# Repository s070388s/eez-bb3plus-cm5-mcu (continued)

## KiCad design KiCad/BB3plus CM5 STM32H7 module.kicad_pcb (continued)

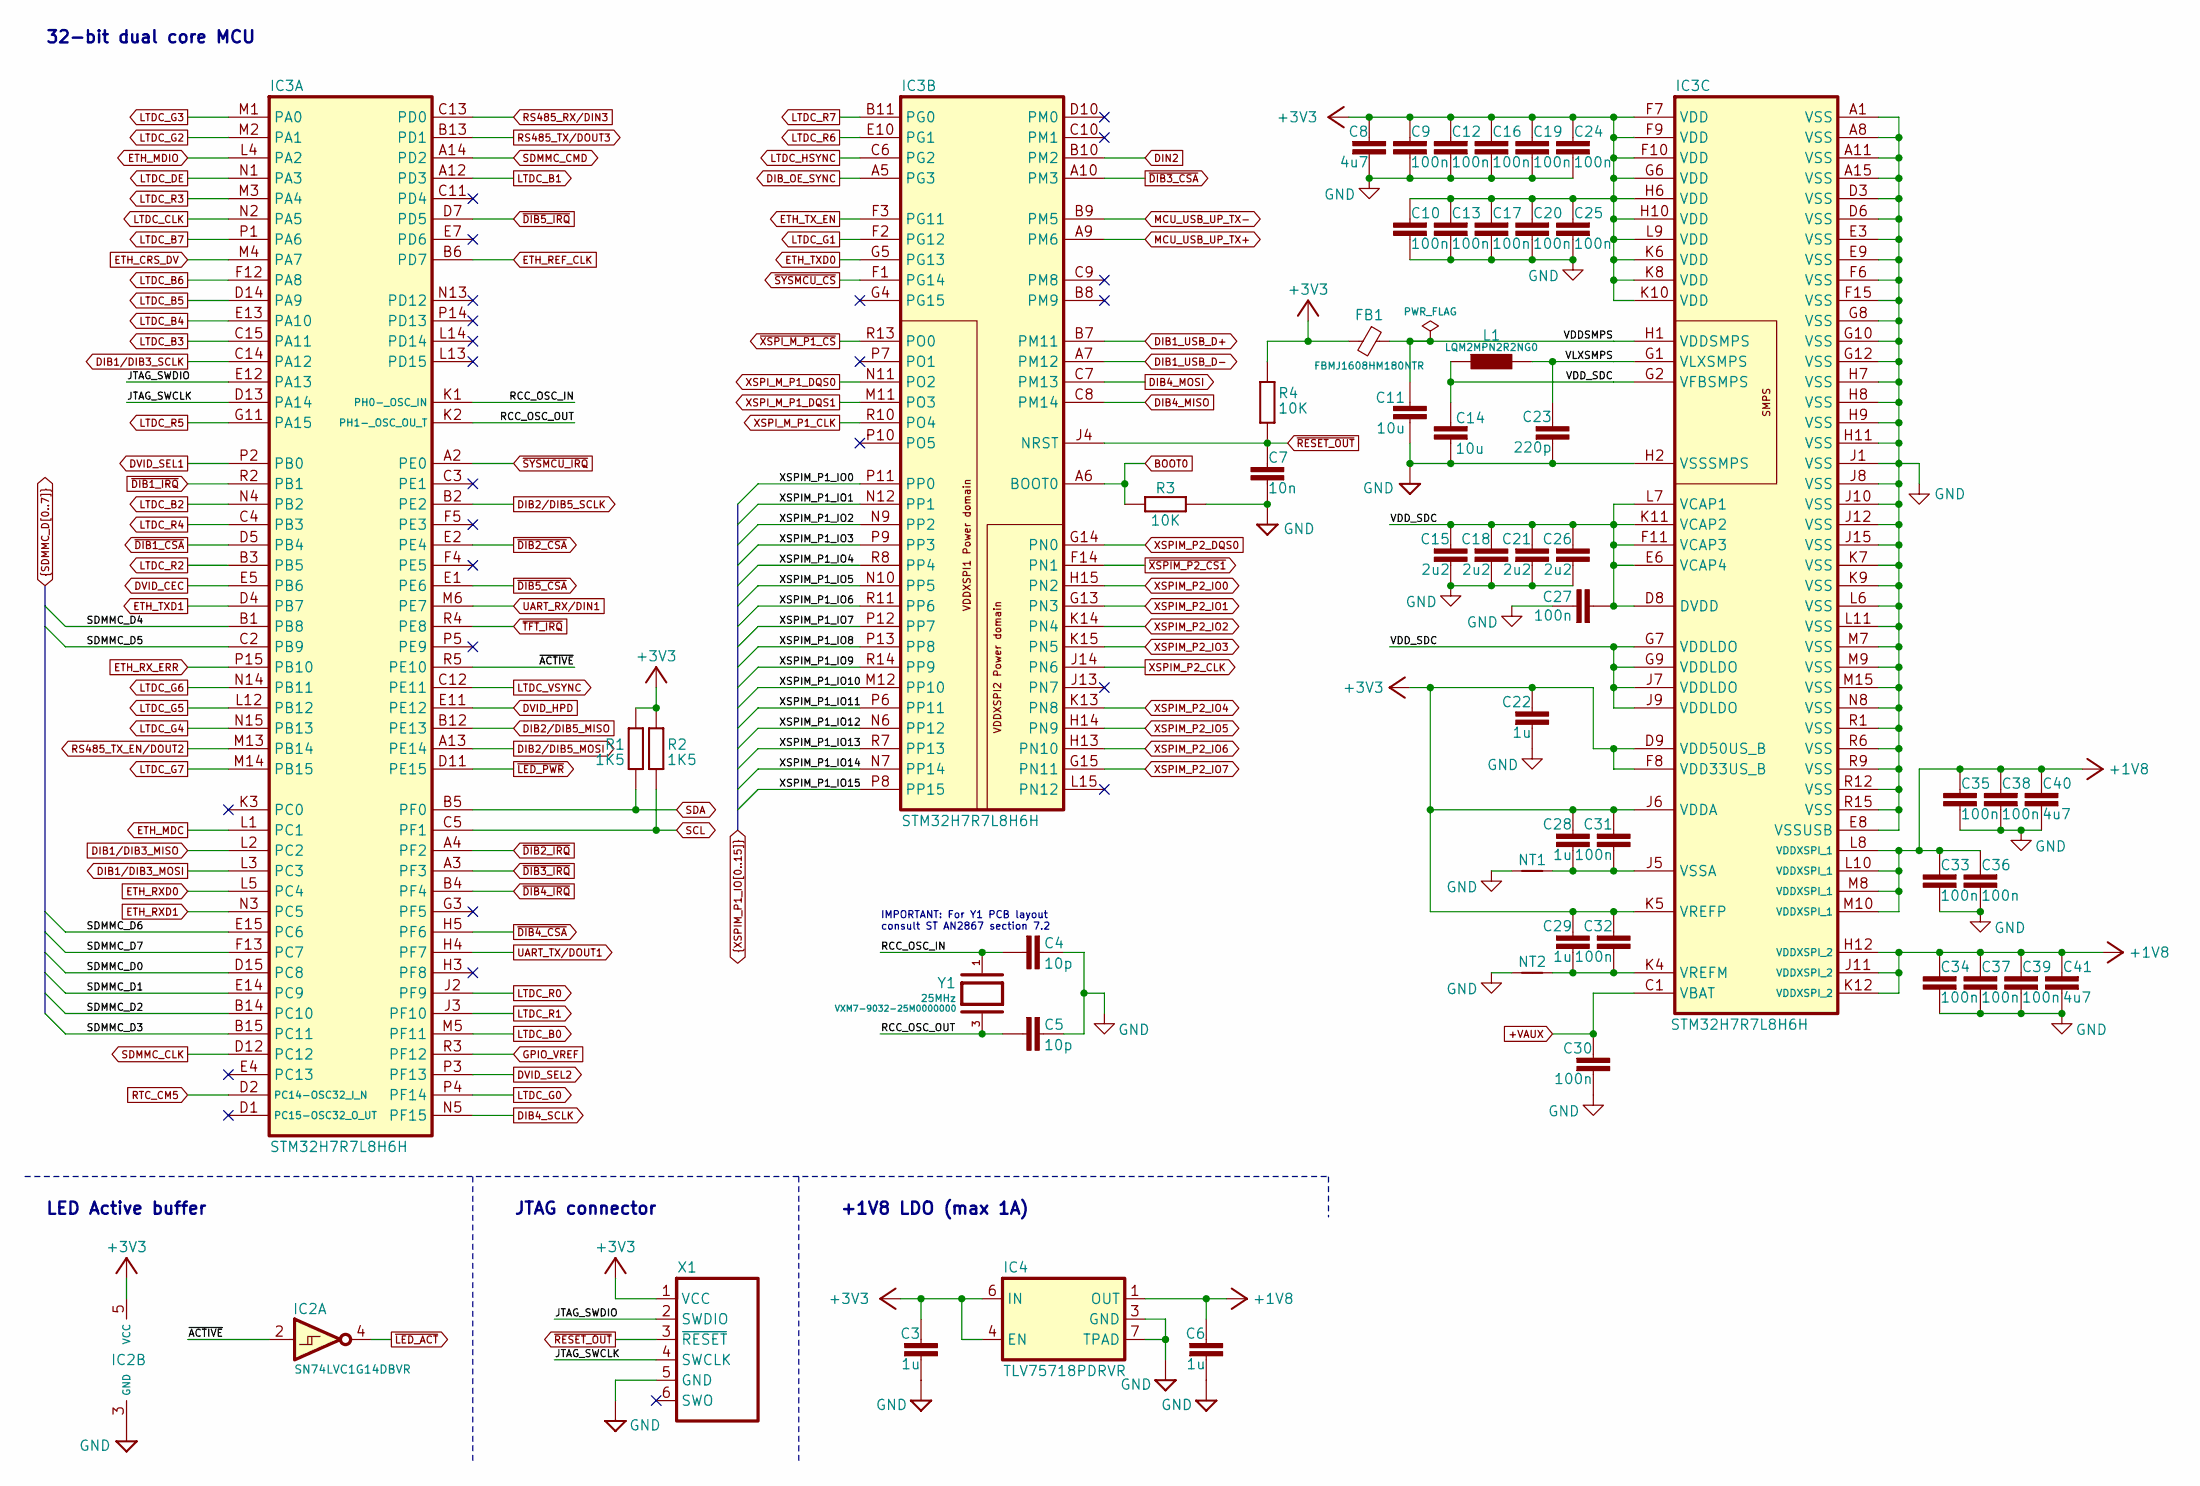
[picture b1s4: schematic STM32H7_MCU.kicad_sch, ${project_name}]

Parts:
C3, C6, C22, C28, C29: 1u; C_0402_1005Metric; DigiKey 490-GRM155C81A105MA12DCT-ND
C4, C5: 10p; C_0402_1005Metric; DigiKey 490-7299-1-ND
C7: 10n; C_0402_1005Metric; DigiKey 490-6309-1-ND
C8, C40, C41: 4u7; C_0603_1608Metric; DigiKey 1276-1044-1-ND
C9, C10, C12, C13, C16, C17, C19, C20, C24, C25, C27, C30, C31, C32, C33, C34, C35, C36, C37, C38, C39: 100n; C_0402_1005Metric; DigiKey 490-6287-1-ND
C11, C14: 10u; C_0603_1608Metric; DigiKey 1276-1052-6-ND
C15, C18, C21, C26: 2u2; C_0402_1005Metric; DigiKey 490-GRM155C71A225KE11JCT-ND
C23: 220p; C_0402_1005Metric; DigiKey 1276-6762-1-ND
FB1: FBMJ1608HM180NTR; BEAD0603; DigiKey 587-3251-2-ND
IC2: SN74LVC1G14DBVR; DBV5; DigiKey 296-11607-1-ND
IC3: STM32H7R7L8H6H; TFBGA225_13X13_STM; DigiKey 497-STM32H7R7L8H6H-ND
IC4: TLV75718PDRVR; DRV0006A; DigiKey 296-50006-1-ND
L1: LQM2MPN2R2NG0; 0806; DigiKey 490-7786-2-ND
NT1, NT2: NetTie_2; NetTie-2_SMD_Pad0.2mm
R1, R2: 1K5; R_0402_1005Metric; DigiKey 311-1.50KLRCT-ND
R3, R4: 10K; R_0402_1005Metric; DigiKey 311-10.0KLRCT-ND
X1: TC2030
Y1: VXM7-9032-25M0000000; XTAL_403C11A24M00000; DigiKey 150-VXM7-9032-25M0000000CT-ND

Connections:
+1V8: C6.1, C33.1, C34.1, C35.1, C36.1, C37.1, C38.1, C39.1, C40.1, C41.1, IC3.H12 (VDDXSPI_2), IC3.J11 (VDDXSPI_2), IC3.K12 (VDDXSPI_2), IC3.L8 (VDDXSPI_1), IC3.L10 (VDDXSPI_1), IC3.M8 (VDDXSPI_1), IC3.M10 (VDDXSPI_1), IC4.1 (OUT); also elsewhere on the board
+3V3: C3.1, C8.1, C9.1, C10.1, C12.1, C13.1, C16.1, C17.1, C19.1, C20.1, C22.1, C24.1, C25.1, C28.1, C29.1, C31.1, C32.1, FB1.2, IC2.5 (VCC), IC3.D9 (VDD50US_B), IC3.F7 (VDD), IC3.F8 (VDD33US_B), IC3.F9 (VDD), IC3.F10 (VDD), IC3.G6 (VDD), IC3.H6 (VDD), IC3.H10 (VDD), IC3.J6 (VDDA), IC3.K5 (VREFP), IC3.K6 (VDD), IC3.K8 (VDD), IC3.K10 (VDD), IC3.L9 (VDD), IC4.4 (EN), IC4.6 (IN), R1.2, R2.2, R4.2, X1.1 (VCC); also elsewhere on the board
+VAUX: C30.1, IC3.C1 (VBAT); also elsewhere on the board
/STM32H7 MCU/JTAG_SWCLK: IC3.D13 (PA14), X1.4 (SWCLK)
/STM32H7 MCU/JTAG_SWDIO: IC3.E12 (PA13), X1.2 (SWDIO)
/STM32H7 MCU/RCC_OSC_IN: C4.2, IC3.K1 (PH0-_OSC_IN), Y1.1
/STM32H7 MCU/RCC_OSC_OUT: C5.2, IC3.K2 (PH1-_OSC_OU_T), Y1.3
/STM32H7 MCU/VDDSMPS: C11.2, FB1.1, IC3.H1 (VDDSMPS)
/STM32H7 MCU/VDD_SDC: C14.2, C15.1, C18.1, C21.1, C26.1, C27.2, IC3.D8 (DVDD), IC3.E6 (VCAP4), IC3.F11 (VCAP3), IC3.G2 (VFBSMPS), IC3.G7 (VDDLDO), IC3.G9 (VDDLDO), IC3.J7 (VDDLDO), IC3.J9 (VDDLDO), IC3.K11 (VCAP2), IC3.L7 (VCAP1), L1.1
/STM32H7 MCU/VLXSMPS: C23.1, IC3.G1 (VLXSMPS), L1.2
/STM32H7 MCU/~ACTIVE: IC2.2 (A), IC3.R5 (PE10)
BOOT0: IC3.A6 (BOOT0), R3.1; also elsewhere on the board
DIB1_USB_D+: IC3.B7 (PM11); also elsewhere on the board
DIB1_USB_D-: IC3.A7 (PM12); also elsewhere on the board
DIB1/DIB3_MISO: IC3.L2 (PC2); also elsewhere on the board
DIB1/DIB3_MOSI: IC3.L3 (PC3); also elsewhere on the board
DIB1/DIB3_SCLK: IC3.C14 (PA12); also elsewhere on the board
DIB2/DIB5_MISO: IC3.B12 (PE13); also elsewhere on the board
DIB2/DIB5_MOSI: IC3.A13 (PE14); also elsewhere on the board
DIB2/DIB5_SCLK: IC3.B2 (PE2); also elsewhere on the board
DIB4_MISO: IC3.C8 (PM14); also elsewhere on the board
DIB4_MOSI: IC3.C7 (PM13); also elsewhere on the board
DIB4_SCLK: IC3.N5 (PF15); also elsewhere on the board
DIB_OE_SYNC: IC3.A5 (PG3); also elsewhere on the board
DIN2: IC3.B10 (PM2); also elsewhere on the board
DVID_CEC: IC3.E5 (PB6); also elsewhere on the board
DVID_HPD: IC3.E11 (PE12); also elsewhere on the board
DVID_SEL1: IC3.P2 (PB0); also elsewhere on the board
DVID_SEL2: IC3.P3 (PF13); also elsewhere on the board
ETH_CRS_DV: IC3.M4 (PA7); also elsewhere on the board
ETH_MDC: IC3.L1 (PC1); also elsewhere on the board
ETH_MDIO: IC3.L4 (PA2); also elsewhere on the board
ETH_REF_CLK: IC3.B6 (PD7); also elsewhere on the board
ETH_RXD0: IC3.L5 (PC4); also elsewhere on the board
ETH_RXD1: IC3.N3 (PC5); also elsewhere on the board
ETH_RX_ERR: IC3.P15 (PB10); also elsewhere on the board
ETH_TXD0: IC3.G5 (PG13); also elsewhere on the board
ETH_TXD1: IC3.D4 (PB7); also elsewhere on the board
ETH_TX_EN: IC3.F3 (PG11); also elsewhere on the board
GND: C3.2, C4.1, C5.1, C6.2, C7.2, C8.2, C9.2, C10.2, C11.1, C12.2, C13.2, C14.1, C15.2, C16.2, C17.2, C18.2, C19.2, C20.2, C21.2, C22.2, C23.2, C24.2, C25.2, C26.2, C27.1, C30.2, C33.2, C34.2, C35.2, C36.2, C37.2, C38.2, C39.2, C40.2, C41.2, IC2.3 (GND), IC3.A1 (VSS), IC3.A8 (VSS), IC3.A11 (VSS), IC3.A15 (VSS), IC3.D3 (VSS), IC3.D6 (VSS), IC3.E3 (VSS), IC3.E8 (VSSUSB), IC3.E9 (VSS), IC3.F6 (VSS), IC3.F15 (VSS), IC3.G8 (VSS), IC3.G10 (VSS), IC3.G12 (VSS), IC3.H2 (VSSSMPS), IC3.H7 (VSS), IC3.H8 (VSS), IC3.H9 (VSS), IC3.H11 (VSS), IC3.J1 (VSS), IC3.J8 (VSS), IC3.J10 (VSS), IC3.J12 (VSS), IC3.J15 (VSS), IC3.K7 (VSS), IC3.K9 (VSS), IC3.L6 (VSS), IC3.L11 (VSS), IC3.M7 (VSS), IC3.M9 (VSS), IC3.M15 (VSS), IC3.N8 (VSS), IC3.R1 (VSS), IC3.R6 (VSS), IC3.R9 (VSS), IC3.R12 (VSS), IC3.R15 (VSS), IC4.3 (GND), IC4.7 (TPAD), NT1.1, NT2.1, R3.2, X1.5 (GND); also elsewhere on the board
GPIO_VREF: IC3.R3 (PF12); also elsewhere on the board
LTDC_B0: IC3.M5 (PF11); also elsewhere on the board
LTDC_B1: IC3.A12 (PD3); also elsewhere on the board
LTDC_B2: IC3.N4 (PB2); also elsewhere on the board
LTDC_B3: IC3.C15 (PA11); also elsewhere on the board
LTDC_B4: IC3.E13 (PA10); also elsewhere on the board
LTDC_B5: IC3.D14 (PA9); also elsewhere on the board
LTDC_B6: IC3.F12 (PA8); also elsewhere on the board
LTDC_B7: IC3.P1 (PA6); also elsewhere on the board
LTDC_CLK: IC3.N2 (PA5); also elsewhere on the board
LTDC_DE: IC3.N1 (PA3); also elsewhere on the board
LTDC_G0: IC3.P4 (PF14); also elsewhere on the board
LTDC_G1: IC3.F2 (PG12); also elsewhere on the board
LTDC_G2: IC3.M2 (PA1); also elsewhere on the board
LTDC_G3: IC3.M1 (PA0); also elsewhere on the board
LTDC_G4: IC3.N15 (PB13); also elsewhere on the board
LTDC_G5: IC3.L12 (PB12); also elsewhere on the board
LTDC_G6: IC3.N14 (PB11); also elsewhere on the board
LTDC_G7: IC3.M14 (PB15); also elsewhere on the board
LTDC_HSYNC: IC3.C6 (PG2); also elsewhere on the board
LTDC_R0: IC3.J2 (PF9); also elsewhere on the board
LTDC_R1: IC3.J3 (PF10); also elsewhere on the board
LTDC_R2: IC3.B3 (PB5); also elsewhere on the board
LTDC_R3: IC3.M3 (PA4); also elsewhere on the board
LTDC_R4: IC3.C4 (PB3); also elsewhere on the board
LTDC_R5: IC3.G11 (PA15); also elsewhere on the board
LTDC_R6: IC3.E10 (PG1); also elsewhere on the board
LTDC_R7: IC3.B11 (PG0); also elsewhere on the board
LTDC_VSYNC: IC3.C12 (PE11); also elsewhere on the board
MCU_USB_UP_TX+: IC3.A9 (PM6); also elsewhere on the board
MCU_USB_UP_TX-: IC3.B9 (PM5); also elsewhere on the board
unnamed: C29.2, C32.2, IC3.K4 (VREFM), NT2.2
unnamed: C28.2, C31.2, IC3.J5 (VSSA), NT1.2
RS485_RX/DIN3: IC3.C13 (PD0); also elsewhere on the board
RS485_TX_EN/DOUT2: IC3.M13 (PB14); also elsewhere on the board
RS485_TX/DOUT3: IC3.B13 (PD1); also elsewhere on the board
RTC_CM5: IC3.D2 (PC14-OSC32_I_N); also elsewhere on the board
SCL: IC3.C5 (PF1), R2.1; also elsewhere on the board
SDA: IC3.B5 (PF0), R1.1; also elsewhere on the board
SDMMC_CLK: IC3.D12 (PC12); also elsewhere on the board
SDMMC_CMD: IC3.A14 (PD2); also elsewhere on the board
SDMMC_D0: IC3.D15 (PC8); also elsewhere on the board
SDMMC_D1: IC3.E14 (PC9); also elsewhere on the board
SDMMC_D2: IC3.B14 (PC10); also elsewhere on the board
SDMMC_D3: IC3.B15 (PC11); also elsewhere on the board
SDMMC_D4: IC3.B1 (PB8); also elsewhere on the board
SDMMC_D5: IC3.C2 (PB9); also elsewhere on the board
SDMMC_D6: IC3.E15 (PC6); also elsewhere on the board
SDMMC_D7: IC3.F13 (PC7); also elsewhere on the board
UART_RX/DIN1: IC3.M6 (PE7); also elsewhere on the board
UART_TX/DOUT1: IC3.H4 (PF7); also elsewhere on the board
XSPIM_P1_IO0: IC3.P11 (PP0); also elsewhere on the board
XSPIM_P1_IO1: IC3.N12 (PP1); also elsewhere on the board
XSPIM_P1_IO2: IC3.N9 (PP2); also elsewhere on the board
XSPIM_P1_IO3: IC3.P9 (PP3); also elsewhere on the board
XSPIM_P1_IO4: IC3.R8 (PP4); also elsewhere on the board
XSPIM_P1_IO5: IC3.N10 (PP5); also elsewhere on the board
XSPIM_P1_IO6: IC3.R11 (PP6); also elsewhere on the board
XSPIM_P1_IO7: IC3.P12 (PP7); also elsewhere on the board
XSPIM_P1_IO8: IC3.P13 (PP8); also elsewhere on the board
XSPIM_P1_IO9: IC3.R14 (PP9); also elsewhere on the board
XSPIM_P1_IO10: IC3.M12 (PP10); also elsewhere on the board
XSPIM_P1_IO11: IC3.P6 (PP11); also elsewhere on the board
XSPIM_P1_IO12: IC3.N6 (PP12); also elsewhere on the board
XSPIM_P1_IO13: IC3.R7 (PP13); also elsewhere on the board
XSPIM_P1_IO14: IC3.N7 (PP14); also elsewhere on the board
XSPIM_P1_IO15: IC3.P8 (PP15); also elsewhere on the board
XSPIM_P2_CLK: IC3.J14 (PN6); also elsewhere on the board
XSPIM_P2_DQS0: IC3.G14 (PN0); also elsewhere on the board
XSPIM_P2_IO0: IC3.H15 (PN2); also elsewhere on the board
XSPIM_P2_IO1: IC3.G13 (PN3); also elsewhere on the board
XSPIM_P2_IO2: IC3.K14 (PN4); also elsewhere on the board
XSPIM_P2_IO3: IC3.K15 (PN5); also elsewhere on the board
XSPIM_P2_IO4: IC3.K13 (PN8); also elsewhere on the board
XSPIM_P2_IO5: IC3.H14 (PN9); also elsewhere on the board
XSPIM_P2_IO6: IC3.H13 (PN10); also elsewhere on the board
XSPIM_P2_IO7: IC3.G15 (PN11); also elsewhere on the board
XSPI_M_P1_CLK: IC3.R10 (PO4); also elsewhere on the board
XSPI_M_P1_DQS0: IC3.N11 (PO2); also elsewhere on the board
XSPI_M_P1_DQS1: IC3.M11 (PO3); also elsewhere on the board
~DIB1_CSA: IC3.D5 (PB4); also elsewhere on the board
~DIB1_IRQ: IC3.R2 (PB1); also elsewhere on the board
~DIB2_CSA: IC3.E2 (PE4); also elsewhere on the board
~DIB2_IRQ: IC3.A4 (PF2); also elsewhere on the board
~DIB3_CSA: IC3.A10 (PM3); also elsewhere on the board
~DIB3_IRQ: IC3.A3 (PF3); also elsewhere on the board
~DIB4_CSA: IC3.H5 (PF6); also elsewhere on the board
~DIB4_IRQ: IC3.B4 (PF4); also elsewhere on the board
~DIB5_CSA: IC3.E1 (PE6); also elsewhere on the board
~DIB5_IRQ: IC3.D7 (PD5); also elsewhere on the board
~LED_ACT: IC2.4 (Y); also elsewhere on the board
~LED_PWR: IC3.D11 (PE15); also elsewhere on the board
~RESET_OUT: C7.1, IC3.J4 (NRST), R4.1, X1.3 (~RESET); also elsewhere on the board
~SYSMCU_CS: IC3.F1 (PG14); also elsewhere on the board
~SYSMCU_IRQ: IC3.A2 (PE0); also elsewhere on the board
~TFT_IRQ: IC3.R4 (PE8); also elsewhere on the board
~XSPIM_P2_CS1: IC3.F14 (PN1); also elsewhere on the board
~XSPI_M_P1_CS: IC3.R13 (PO0); also elsewhere on the board

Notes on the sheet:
32-bit dual core MCU
LED Active buffer
JTAG connector
IMPORTANT: For Y1 PCB layout consult ST AN2867 section 7.2
+1V8 LDO (max 1A)

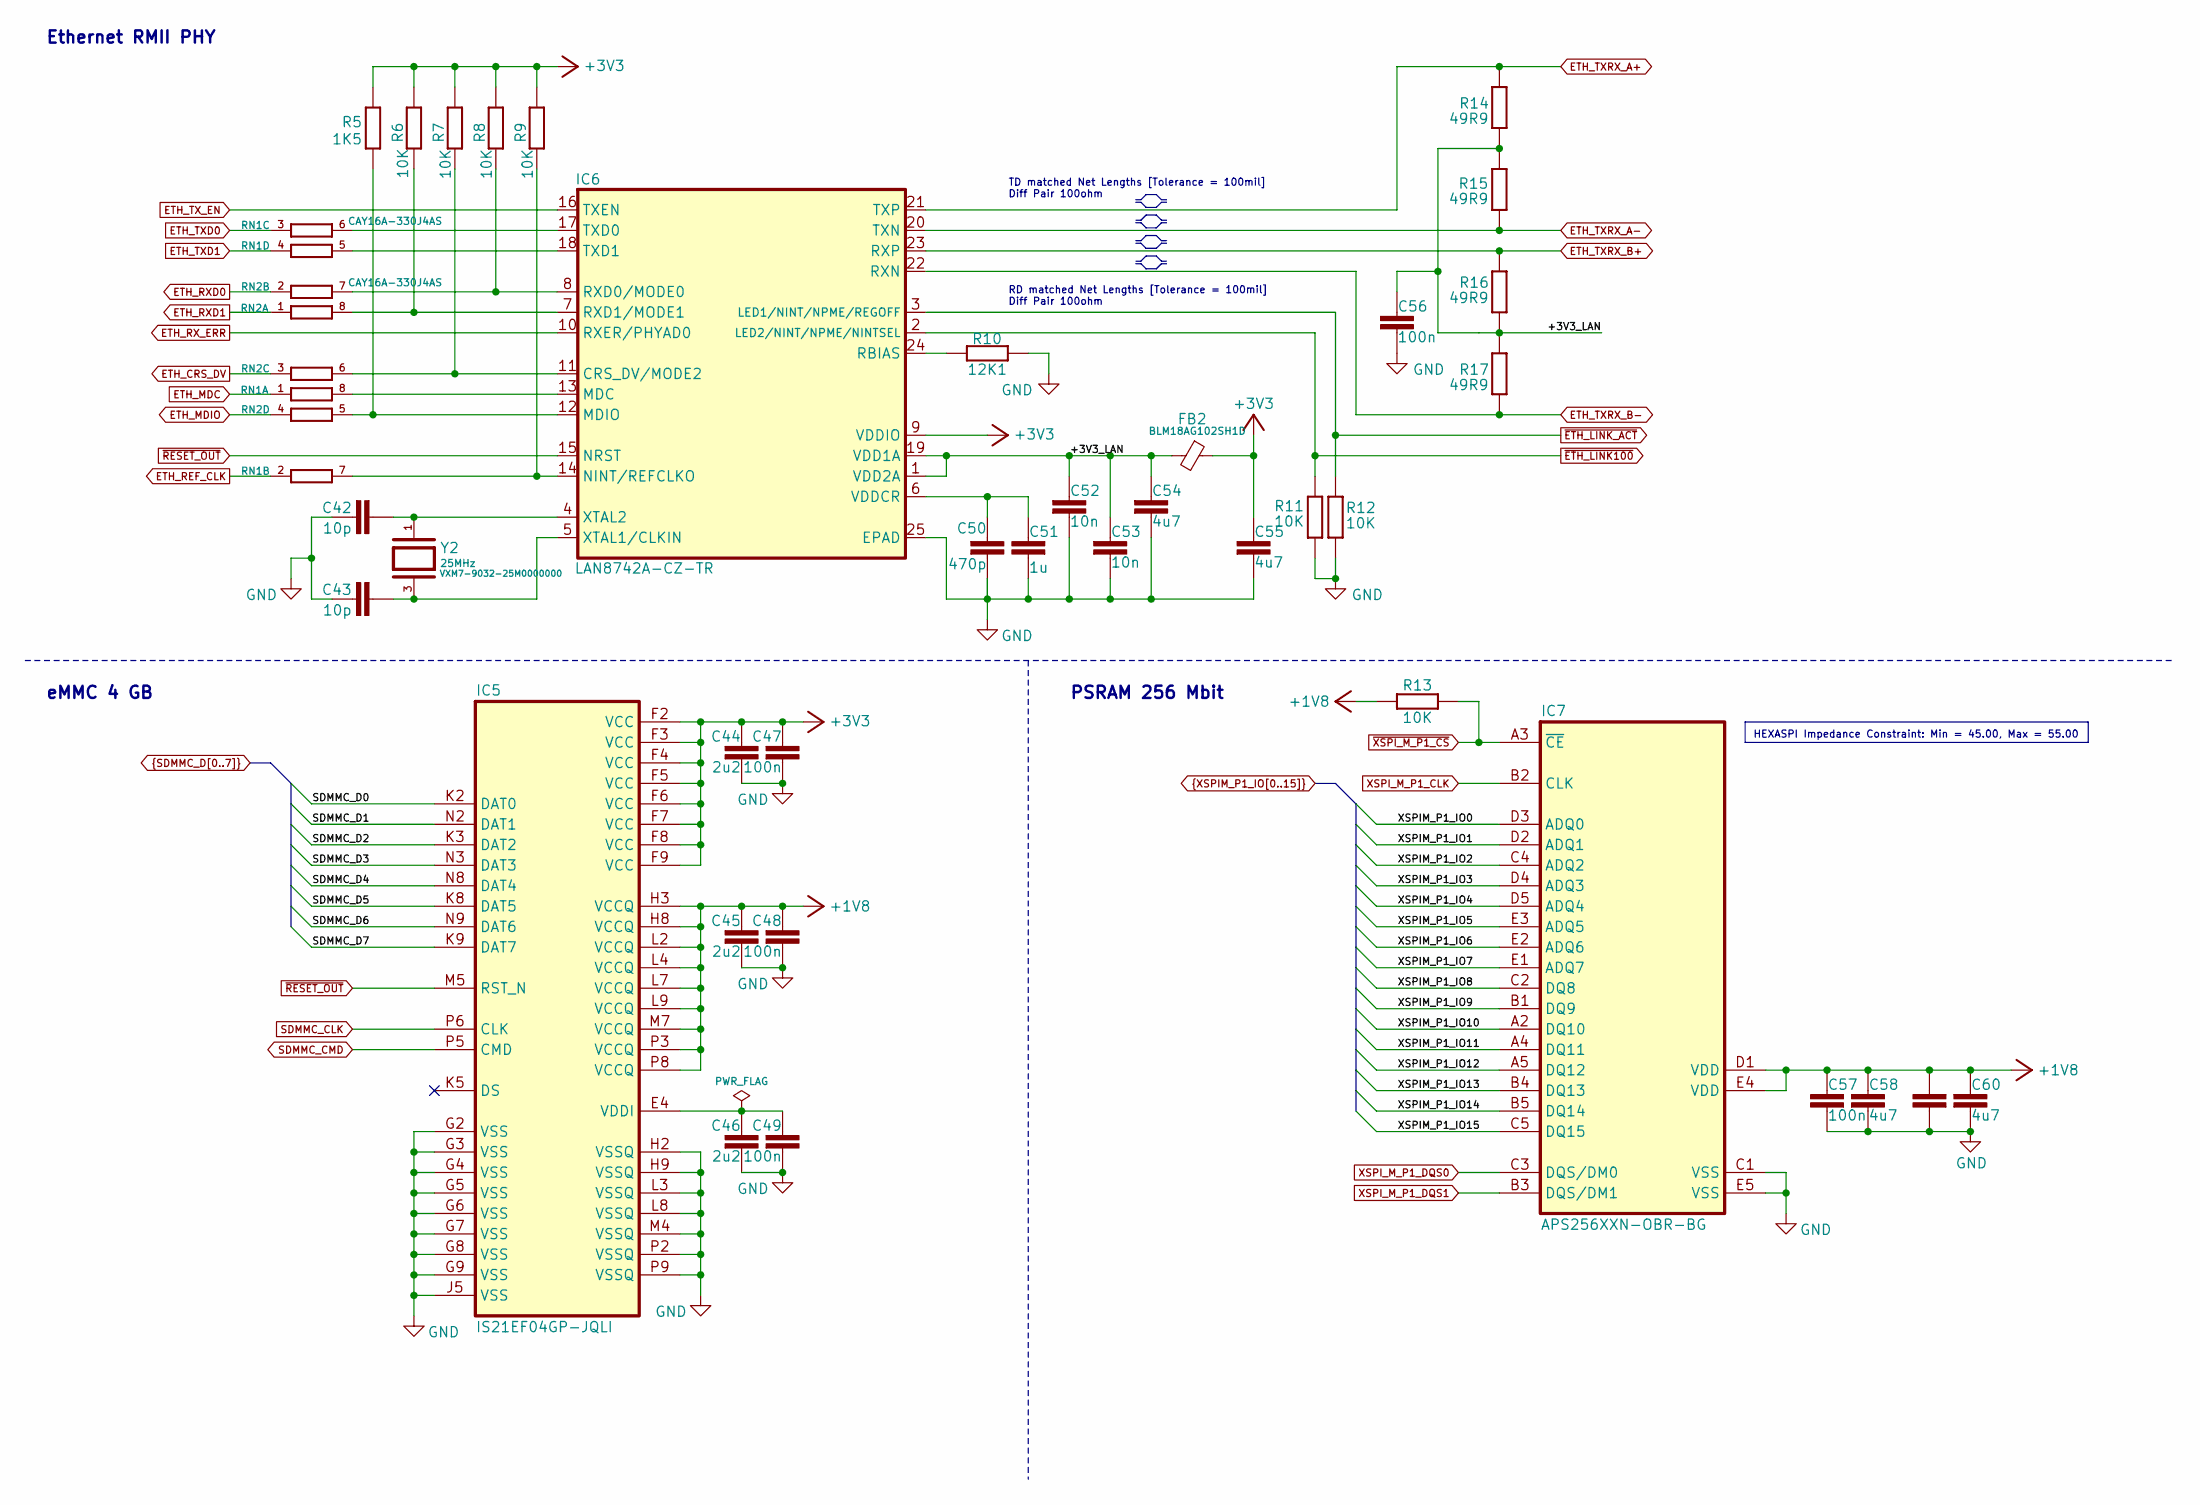
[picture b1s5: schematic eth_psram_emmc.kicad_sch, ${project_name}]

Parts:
C42, C43: 10p; C_0402_1005Metric; DigiKey 490-7299-1-ND
C44, C45, C46: 2u2; C_0402_1005Metric; DigiKey 490-GRM155C71A225KE11JCT-ND
C47, C48, C49, C56, C57, C59: 100n; C_0402_1005Metric; DigiKey 490-6287-1-ND
C50: 470p; C_0402_1005Metric; DigiKey 1276-1117-1-ND
C51: 1u; C_0402_1005Metric; DigiKey 490-GRM155C81A105MA12DCT-ND
C52, C53: 10n; C_0402_1005Metric; DigiKey 490-6309-1-ND
C54, C55, C58, C60: 4u7; C_0603_1608Metric; DigiKey 1276-1044-1-ND
FB2: BLM18AG102SH1D; BEAD0603; DigiKey 490-7809-1-ND
IC5: IS21EF04GP-JQLI; DigiKey 706-IS21EF04GP-JQLI-ND
IC6: LAN8742A-CZ-TR; SQFN24_4X4MC_MCH-M; DigiKey LAN8742A-CZ-CT-ND
IC7: APS256XXN-OBR-BG; APS256XXN-OBR-BG_APY-L; Mouser 878-APS256XXN-OB9-BG
R5: 1K5; R_0402_1005Metric; DigiKey 311-1.50KLRCT-ND
R6, R7, R8, R9, R11, R12, R13: 10K; R_0402_1005Metric; DigiKey 311-10.0KLRCT-ND
R10: 12K1; R_0402_1005Metric; DigiKey 13-RC0402FR-1012K1LCT-ND
R14, R15, R16, R17: 49R9; R_0402_1005Metric; DigiKey 13-RC0402FR-1349R9LCT-ND
RN1, RN2: CAY16A-330J4AS; CAY16; DigiKey CAY16-330J4LFCT-ND
Y2: VXM7-9032-25M0000000; XTAL_403C11A24M00000; DigiKey 150-VXM7-9032-25M0000000CT-ND

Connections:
+1V8: C45.1, C48.1, C57.1, C58.1, C59.1, C60.1, IC5.H3 (VCCQ), IC5.H8 (VCCQ), IC5.L2 (VCCQ), IC5.L4 (VCCQ), IC5.L7 (VCCQ), IC5.L9 (VCCQ), IC5.M7 (VCCQ), IC5.P3 (VCCQ), IC5.P8 (VCCQ), IC7.D1 (VDD), IC7.E4 (VDD), R13.2; also elsewhere on the board
+3V3: C44.1, C47.1, C55.1, FB2.1, IC5.F2 (VCC), IC5.F3 (VCC), IC5.F4 (VCC), IC5.F5 (VCC), IC5.F6 (VCC), IC5.F7 (VCC), IC5.F8 (VCC), IC5.F9 (VCC), IC6.9 (VDDIO), R5.2, R6.1, R7.2, R8.2, R9.2; also elsewhere on the board
/Ethernet PHY, PSRAM, eMMC/+3V3_LAN: C52.1, C53.1, C54.1, C56.2, FB2.2, IC6.1 (VDD2A), IC6.19 (VDD1A), R14.1, R15.1, R16.1, R17.2
ETH_CRS_DV: RN2.3 (1); also elsewhere on the board
ETH_MDC: RN1.1; also elsewhere on the board
ETH_MDIO: RN2.4 (1); also elsewhere on the board
ETH_REF_CLK: RN1.2 (1); also elsewhere on the board
ETH_RXD0: RN2.2 (1); also elsewhere on the board
ETH_RXD1: RN2.1; also elsewhere on the board
ETH_RX_ERR: IC6.10 (RXER/PHYAD0); also elsewhere on the board
ETH_TXD0: RN1.3 (1); also elsewhere on the board
ETH_TXD1: RN1.4 (1); also elsewhere on the board
ETH_TXRX_A+: IC6.21 (TXP), R14.2; also elsewhere on the board
ETH_TXRX_A-: IC6.20 (TXN), R15.2; also elsewhere on the board
ETH_TXRX_B+: IC6.23 (RXP), R16.2; also elsewhere on the board
ETH_TXRX_B-: IC6.22 (RXN), R17.1; also elsewhere on the board
ETH_TX_EN: IC6.16 (TXEN); also elsewhere on the board
GND: C42.1, C43.1, C44.2, C45.2, C46.2, C47.2, C48.2, C49.2, C50.2, C51.1, C52.2, C53.2, C54.2, C55.2, C56.1, C57.2, C58.2, C59.2, C60.2, IC5.G2 (VSS), IC5.G3 (VSS), IC5.G4 (VSS), IC5.G5 (VSS), IC5.G6 (VSS), IC5.G7 (VSS), IC5.G8 (VSS), IC5.G9 (VSS), IC5.H2 (VSSQ), IC5.H9 (VSSQ), IC5.J5 (VSS), IC5.L3 (VSSQ), IC5.L8 (VSSQ), IC5.M4 (VSSQ), IC5.P2 (VSSQ), IC5.P9 (VSSQ), IC6.25 (EPAD), IC7.C1 (VSS), IC7.E5 (VSS), R10.2, R11.2, R12.1; also elsewhere on the board
unnamed: C46.1, C49.1, IC5.E4 (VDDI)
unnamed: IC6.11 (CRS_DV/MODE2), R7.1, RN2.6 (2)
unnamed: IC6.13 (MDC), RN1.8 (2)
unnamed: IC6.12 (MDIO), R5.1, RN2.5 (2)
unnamed: IC6.14 (NINT/REFCLKO), R9.1, RN1.7 (2)
unnamed: IC6.24 (RBIAS), R10.1
unnamed: IC6.8 (RXD0/MODE0), R8.1, RN2.7 (2)
unnamed: IC6.7 (RXD1/MODE1), R6.2, RN2.8 (2)
unnamed: IC6.17 (TXD0), RN1.6 (2)
unnamed: IC6.18 (TXD1), RN1.5 (2)
unnamed: C50.1, C51.2, IC6.6 (VDDCR)
unnamed: C43.2, IC6.5 (XTAL1/CLKIN), Y2.3
unnamed: C42.2, IC6.4 (XTAL2), Y2.1
SDMMC_CLK: IC5.P6 (CLK); also elsewhere on the board
SDMMC_CMD: IC5.P5 (CMD); also elsewhere on the board
SDMMC_D0: IC5.K2 (DAT0); also elsewhere on the board
SDMMC_D1: IC5.N2 (DAT1); also elsewhere on the board
SDMMC_D2: IC5.K3 (DAT2); also elsewhere on the board
SDMMC_D3: IC5.N3 (DAT3); also elsewhere on the board
SDMMC_D4: IC5.N8 (DAT4); also elsewhere on the board
SDMMC_D5: IC5.K8 (DAT5); also elsewhere on the board
SDMMC_D6: IC5.N9 (DAT6); also elsewhere on the board
SDMMC_D7: IC5.K9 (DAT7); also elsewhere on the board
XSPIM_P1_IO0: IC7.D3 (ADQ0); also elsewhere on the board
XSPIM_P1_IO1: IC7.D2 (ADQ1); also elsewhere on the board
XSPIM_P1_IO2: IC7.C4 (ADQ2); also elsewhere on the board
XSPIM_P1_IO3: IC7.D4 (ADQ3); also elsewhere on the board
XSPIM_P1_IO4: IC7.D5 (ADQ4); also elsewhere on the board
XSPIM_P1_IO5: IC7.E3 (ADQ5); also elsewhere on the board
XSPIM_P1_IO6: IC7.E2 (ADQ6); also elsewhere on the board
XSPIM_P1_IO7: IC7.E1 (ADQ7); also elsewhere on the board
XSPIM_P1_IO8: IC7.C2 (DQ8); also elsewhere on the board
XSPIM_P1_IO9: IC7.B1 (DQ9); also elsewhere on the board
XSPIM_P1_IO10: IC7.A2 (DQ10); also elsewhere on the board
XSPIM_P1_IO11: IC7.A4 (DQ11); also elsewhere on the board
XSPIM_P1_IO12: IC7.A5 (DQ12); also elsewhere on the board
XSPIM_P1_IO13: IC7.B4 (DQ13); also elsewhere on the board
XSPIM_P1_IO14: IC7.B5 (DQ14); also elsewhere on the board
XSPIM_P1_IO15: IC7.C5 (DQ15); also elsewhere on the board
XSPI_M_P1_CLK: IC7.B2 (CLK); also elsewhere on the board
XSPI_M_P1_DQS0: IC7.C3 (DQS/DM0); also elsewhere on the board
XSPI_M_P1_DQS1: IC7.B3 (DQS/DM1); also elsewhere on the board
~ETH_LINK100: IC6.2 (LED2/NINT/NPME/NINTSEL), R11.1; also elsewhere on the board
~ETH_LINK_ACT: IC6.3 (LED1/NINT/NPME/REGOFF), R12.2; also elsewhere on the board
~RESET_OUT: IC5.M5 (RST_N), IC6.15 (NRST); also elsewhere on the board
~XSPI_M_P1_CS: IC7.A3 (~CE), R13.1; also elsewhere on the board

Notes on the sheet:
TD matched Net Lengths [Tolerance = 100mil] Diff Pair 100ohm
eMMC 4 GB
PSRAM 256 Mbit
Ethernet RMII PHY
RD matched Net Lengths [Tolerance = 100mil] Diff Pair 100ohm
HEXASPI Impedance Constraint: Min = 45.00, Max = 55.00

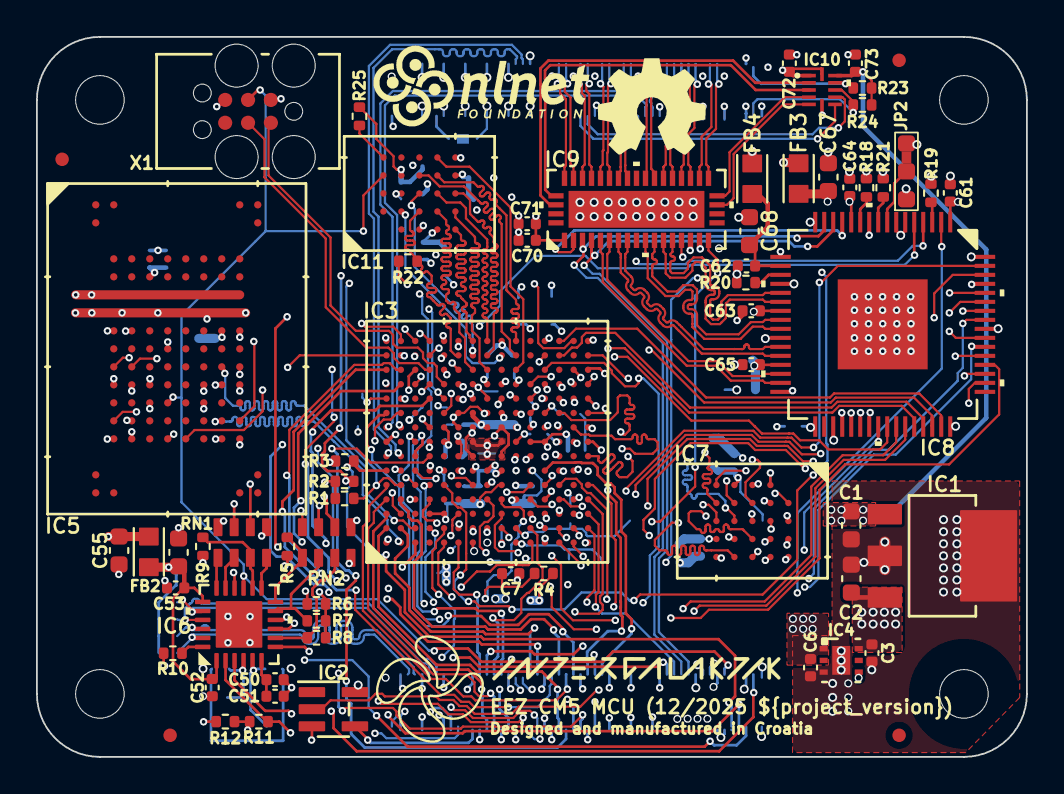
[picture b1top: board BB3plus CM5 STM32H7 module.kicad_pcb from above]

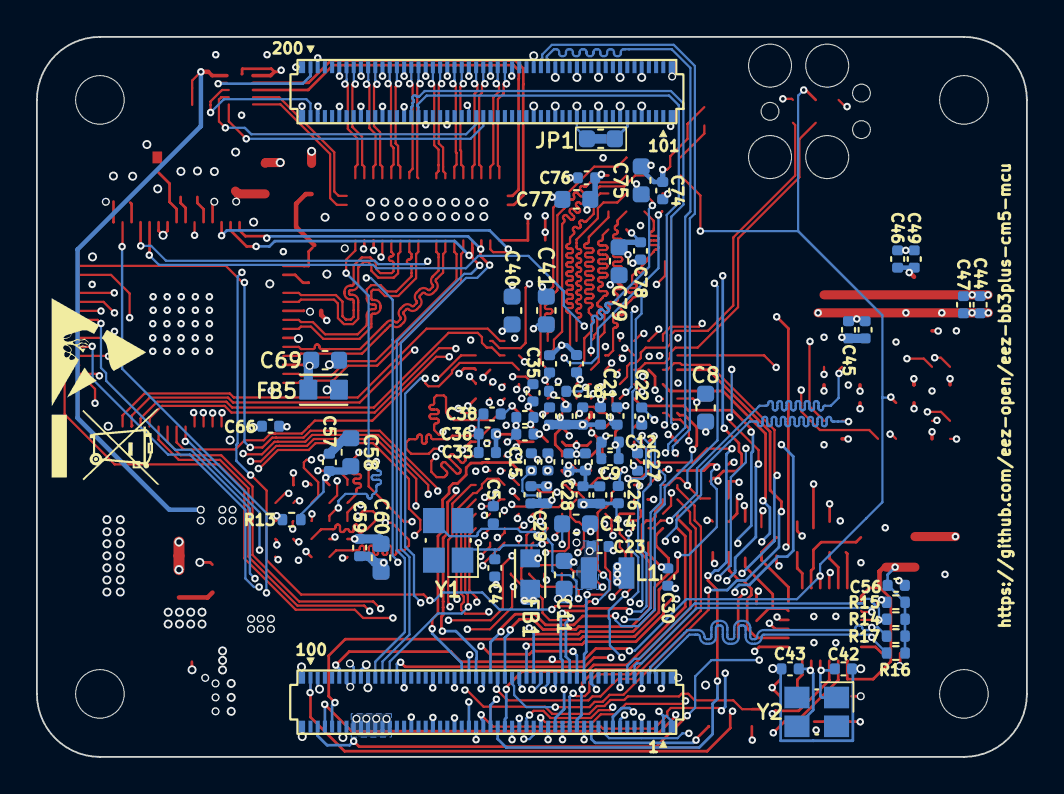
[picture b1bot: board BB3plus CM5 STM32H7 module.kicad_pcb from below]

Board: 6 copper layers, 55.0 x 40.0 mm, 140 parts (72 on the bottom side), 201 nets.

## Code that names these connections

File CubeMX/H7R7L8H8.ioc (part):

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Mcu.Name=STM32H7R7L8HxH
Mcu.Package=TFBGA225 HEXA SMPS
Mcu.UserName=STM32H7R7L8HxH
PA0.GPIOParameters=PinAttribute
PA0.Mode=RGB888
PA0.PinAttribute=Appli
PA0.Signal=LTDC_G3
PA1.GPIOParameters=PinAttribute
PA1.Mode=RGB888
PA1.PinAttribute=Appli
PA1.Signal=LTDC_G2
PA10.GPIOParameters=PinAttribute
PA10.Mode=RGB888
PA10.PinAttribute=Appli
PA10.Signal=LTDC_B4
PA11.GPIOParameters=PinAttribute
PA11.Mode=RGB888
PA11.PinAttribute=Appli
PA11.Signal=LTDC_B3
PA12.GPIOParameters=GPIO_Label,PinAttribute
PA12.GPIO_Label=DIB1/DIB3_SCK
PA12.Mode=Full_Duplex_Master
PA12.PinAttribute=Appli
PA12.Signal=SPI2_SCK
PA13(JTMS/SWDIO).GPIOParameters=GPIO_Label
PA13(JTMS/SWDIO).GPIO_Label=SWDIO
PA13(JTMS/SWDIO).Mode=Serial_Wire
PA13(JTMS/SWDIO).Signal=DEBUG_JTMS-SWDIO
PA14(JTCK/SWCLK).GPIOParameters=GPIO_Label
PA14(JTCK/SWCLK).GPIO_Label=SWCLK
PA14(JTCK/SWCLK).Mode=Serial_Wire
PA14(JTCK/SWCLK).Signal=DEBUG_JTCK-SWCLK
PA15(JTDI).GPIOParameters=PinAttribute
PA15(JTDI).Mode=RGB888
PA15(JTDI).PinAttribute=Appli
PA15(JTDI).Signal=LTDC_R5
PA2.GPIOParameters=PinAttribute
PA2.Mode=RMII
PA2.PinAttribute=Appli
PA2.Signal=ETH_MDIO
PA3.GPIOParameters=PinAttribute
PA3.Mode=RGB888
PA3.PinAttribute=Appli
PA3.Signal=LTDC_DE
PA4.GPIOParameters=PinAttribute
PA4.Mode=RGB888
PA4.PinAttribute=Appli
PA4.Signal=LTDC_R3
PA5.GPIOParameters=PinAttribute
PA5.Mode=RGB888
PA5.PinAttribute=Appli
PA5.Signal=LTDC_CLK
PA6.GPIOParameters=PinAttribute
PA6.Mode=RGB888
PA6.PinAttribute=Appli
PA6.Signal=LTDC_B7
PA7.GPIOParameters=PinAttribute
PA7.Mode=RMII
PA7.PinAttribute=Appli
PA7.Signal=ETH_RMII_CRS_DV
PA8.GPIOParameters=PinAttribute
PA8.Mode=RGB888
PA8.PinAttribute=Appli
PA8.Signal=LTDC_B6
PA9.GPIOParameters=PinAttribute
PA9.Mode=RGB888
PA9.PinAttribute=Appli
PA9.Signal=LTDC_B5
PB0.GPIOParameters=GPIO_Label,PinAttribute
PB0.GPIO_Label=DVID_SEL1
PB0.PinAttribute=Appli
PB0.Signal=GPIO_Output
PB1.GPIOParameters=GPIO_Label,PinAttribute
PB1.GPIO_Label=DIB1_IRQ
PB1.PinAttribute=Free
PB1.Signal=GPXTI1
PB10.GPIOParameters=PinAttribute
PB10.Mode=Activate Rx Err signal
PB10.PinAttribute=Appli
PB10.Signal=ETH_MII_RX_ER
PB11.GPIOParameters=PinAttribute
PB11.Mode=RGB888
PB11.PinAttribute=Appli
PB11.Signal=LTDC_G6
PB12.GPIOParameters=PinAttribute
PB12.Mode=RGB888
PB12.PinAttribute=Appli
PB12.Signal=LTDC_G5
PB13.GPIOParameters=PinAttribute
PB13.Mode=RGB888
PB13.PinAttribute=Appli
PB13.Signal=LTDC_G4
PB14.GPIOParameters=GPIO_Label,PinAttribute
PB14.GPIO_Label=RS485_TX_EN/DOUT2
PB14.Mode=Hardware Flow Control (RS485)
PB14.PinAttribute=Appli
PB14.Signal=UART4_DE
PB15.GPIOParameters=PinAttribute
PB15.Mode=RGB888
PB15.PinAttribute=Appli
PB15.Signal=LTDC_G7
PB2.GPIOParameters=PinAttribute
PB2.Mode=RGB888
PB2.PinAttribute=Appli
PB2.Signal=LTDC_B2
PB3(JTDO/TRACESWO).GPIOParameters=PinAttribute
PB3(JTDO/TRACESWO).Mode=RGB888
PB3(JTDO/TRACESWO).PinAttribute=Appli
PB3(JTDO/TRACESWO).Signal=LTDC_R4
PB4(NJTRST).GPIOParameters=GPIO_Label,PinAttribute
PB4(NJTRST).GPIO_Label=DIB1_CSA
PB4(NJTRST).Mode=NSS_Signal_Hard_Output
PB4(NJTRST).PinAttribute=Appli
PB4(NJTRST).Signal=SPI2_NSS
PB5.GPIOParameters=PinAttribute
PB5.Mode=RGB888
PB5.PinAttribute=Appli
PB5.Signal=LTDC_R2
PB6.GPIOParameters=GPIO_Label,PinAttribute
PB6.GPIO_Label=DVID_CEC
PB6.PinAttribute=Appli
PB6.Signal=CEC
PB7.GPIOParameters=PinAttribute
PB7.Mode=RMII
PB7.PinAttribute=Appli
PB7.Signal=ETH_RMII_TXD1
PB8.GPIOParameters=PinAttribute
PB8.Mode=mmc_8_bits_Wide_bus
PB8.PinAttribute=Appli
PB8.Signal=SDMMC1_D4
PB9.GPIOParameters=PinAttribute
PB9.Mode=mmc_8_bits_Wide_bus
PB9.PinAttribute=Appli
PB9.Signal=SDMMC1_D5
PC1.GPIOParameters=PinAttribute
PC1.Mode=RMII
PC1.PinAttribute=Appli
PC1.Signal=ETH_MDC
PC10.GPIOParameters=PinAttribute
PC10.Mode=mmc_8_bits_Wide_bus
PC10.PinAttribute=Appli
PC10.Signal=SDMMC1_D2
PC11.GPIOParameters=PinAttribute
PC11.Mode=mmc_8_bits_Wide_bus
PC11.PinAttribute=Appli
PC11.Signal=SDMMC1_D3
PC12.GPIOParameters=PinAttribute
PC12.Mode=mmc_8_bits_Wide_bus
PC12.PinAttribute=Appli
PC12.Signal=SDMMC1_CK
PC14-OSC32_IN(OSC32_IN).Mode=LSE-External-Clock-Source
PC14-OSC32_IN(OSC32_IN).Signal=RCC_OSC32_IN
PC2.GPIOParameters=GPIO_Label,PinAttribute
PC2.GPIO_Label=DIB1/DIB3_MISO
PC2.Mode=Full_Duplex_Master
PC2.PinAttribute=Appli
PC2.Signal=SPI2_MISO
PC3.GPIOParameters=GPIO_Label,PinAttribute
PC3.GPIO_Label=DIB1/DIB3_MOSI
PC3.Mode=Full_Duplex_Master
PC3.PinAttribute=Appli
PC3.Signal=SPI2_MOSI
PC4.GPIOParameters=PinAttribute
PC4.Mode=RMII
PC4.PinAttribute=Appli
PC4.Signal=ETH_RMII_RXD0
PC5.GPIOParameters=PinAttribute
PC5.Mode=RMII
PC5.PinAttribute=Appli
PC5.Signal=ETH_RMII_RXD1
PC6.GPIOParameters=PinAttribute
PC6.Mode=mmc_8_bits_Wide_bus
PC6.PinAttribute=Appli
PC6.Signal=SDMMC1_D6
PC7.GPIOParameters=PinAttribute
PC7.Mode=mmc_8_bits_Wide_bus
PC7.PinAttribute=Appli
PC7.Signal=SDMMC1_D7
PC8.GPIOParameters=PinAttribute
PC8.Mode=mmc_8_bits_Wide_bus
PC8.PinAttribute=Appli
PC8.Signal=SDMMC1_D0
PC9.GPIOParameters=PinAttribute
PC9.Mode=mmc_8_bits_Wide_bus
PC9.PinAttribute=Appli
PC9.Signal=SDMMC1_D1
PD0.GPIOParameters=GPIO_Label,PinAttribute
PD0.GPIO_Label=RS485_RX/DIN3
PD0.Mode=Asynchronous
PD0.PinAttribute=Appli
PD0.Signal=UART4_RX
PD1.GPIOParameters=GPIO_Label,PinAttribute
PD1.GPIO_Label=RS485_TX/DOUT3
PD1.Mode=Asynchronous
PD1.PinAttribute=Appli
PD1.Signal=UART4_TX
PD14.GPIOParameters=GPIO_Label
PD14.GPIO_Label=USB_FS_SEL
PD14.Signal=GPIO_Output
PD2.GPIOParameters=PinAttribute
PD2.Mode=mmc_8_bits_Wide_bus
PD2.PinAttribute=Appli
PD2.Signal=SDMMC1_CMD
PD3.GPIOParameters=PinAttribute
PD3.Mode=RGB888
PD3.PinAttribute=Appli
PD3.Signal=LTDC_B1
PD5.GPIOParameters=GPIO_Label,PinAttribute
PD5.GPIO_Label=DIB5_IRQ
PD5.PinAttribute=Free
PD5.Signal=GPXTI5
PD6.GPIOParameters=PinAttribute
PD6.Mode=Digital_ClockEthClk
PD6.PinAttribute=Free
PD6.Signal=ETH_CLK
PD7.GPIOParameters=PinAttribute
PD7.Mode=RMII
PD7.PinAttribute=Appli
PD7.Signal=ETH_RMII_REF_CLK
PE0.GPIOParameters=GPIO_Label,PinAttribute
PE0.GPIO_Label=SYSMCU_IRQ
PE0.PinAttribute=Free
PE0.Signal=GPXTI0
PE10.GPIOParameters=GPIO_Label,PinAttribute
PE10.GPIO_Label=LED_nACT
PE10.PinAttribute=Free
PE10.Signal=GPIO_Output
PE11.GPIOParameters=PinAttribute
PE11.Mode=RGB888
PE11.PinAttribute=Appli
PE11.Signal=LTDC_VSYNC
PE12.GPIOParameters=GPIO_Label,PinAttribute
PE12.GPIO_Label=DVID_HPA
PE12.PinAttribute=Free
PE12.Signal=GPXTI12
PE13.GPIOParameters=GPIO_Label,PinAttribute
PE13.GPIO_Label=DIB2/DIB5_MISO
PE13.Mode=Full_Duplex_Master
PE13.PinAttribute=Appli
PE13.Signal=SPI4_MISO
PE14.GPIOParameters=GPIO_Label,PinAttribute
PE14.GPIO_Label=DIB2/DIB5_MOSI
PE14.Mode=Full_Duplex_Master
PE14.PinAttribute=Appli
PE14.Signal=SPI4_MOSI
PE15.GPIOParameters=GPIO_Label,PinAttribute
PE15.GPIO_Label=LCD_ON
PE15.PinAttribute=Free
PE15.Signal=GPIO_Output
PE2.GPIOParameters=GPIO_Label,PinAttribute
PE2.GPIO_Label=DIB2/DIB5_SCK
PE2.Mode=Full_Duplex_Master
PE2.PinAttribute=Appli
PE2.Signal=SPI4_SCK
PE4.GPIOParameters=GPIO_Label,PinAttribute
PE4.GPIO_Label=DIB2_CSA
PE4.Mode=NSS_Signal_Hard_Output
PE4.PinAttribute=Appli
PE4.Signal=SPI4_NSS
PE6.GPIOParameters=GPIO_Label,PinAttribute
PE6.GPIO_Label=DIB5_CSA
PE6.PinAttribute=Free
PE6.Signal=GPIO_Output
PE7.GPIOParameters=GPIO_Label,PinAttribute
PE7.GPIO_Label=UART_RX/DIN1
PE7.Mode=Asynchronous
PE7.PinAttribute=Appli
PE7.Signal=UART7_RX
PE8.GPIOParameters=GPIO_Label,PinAttribute
PE8.GPIO_Label=TFT_IRQ
PE8.PinAttribute=Free
PE8.Signal=GPXTI8
PF0.GPIOParameters=GPIO_Label,PinAttribute
PF0.GPIO_Label=SDA
PF0.Mode=I2C
PF0.PinAttribute=Appli
PF0.Signal=I2C2_SDA
PF1.GPIOParameters=GPIO_Label,PinAttribute
PF1.GPIO_Label=SCL
PF1.Mode=I2C
PF1.PinAttribute=Appli
PF1.Signal=I2C2_SCL
PF10.GPIOParameters=PinAttribute
PF10.Mode=RGB888
PF10.PinAttribute=Appli
PF10.Signal=LTDC_R1
PF11.GPIOParameters=PinAttribute
PF11.Mode=RGB888
PF11.PinAttribute=Appli
PF11.Signal=LTDC_B0
PF13.GPIOParameters=GPIO_Label,PinAttribute
PF13.GPIO_Label=DVID_SEL2
PF13.PinAttribute=Appli
PF13.Signal=GPIO_Output
PF14.GPIOParameters=PinAttribute
PF14.Mode=RGB888
PF14.PinAttribute=Appli
PF14.Signal=LTDC_G0
PF15.GPIOParameters=GPIO_Label,PinAttribute
PF15.GPIO_Label=DIB4_SCK
PF15.Mode=Full_Duplex_Master
PF15.PinAttribute=Appli
PF15.Signal=SPI5_SCK
PF2.GPIOParameters=GPIO_Label,PinAttribute
PF2.GPIO_Label=DIB2_IRQ
PF2.PinAttribute=Free
PF2.Signal=GPXTI2
PF3.GPIOParameters=GPIO_Label,PinAttribute
PF3.GPIO_Label=DIB3_IRQ
PF3.PinAttribute=Free
PF3.Signal=GPXTI3
PF4.GPIOParameters=GPIO_Label,PinAttribute
PF4.GPIO_Label=DIB4_IRQ
PF4.PinAttribute=Free
PF4.Signal=GPXTI4
PF6.GPIOParameters=GPIO_Label,PinAttribute
PF6.GPIO_Label=DIB4_CSA
PF6.Mode=NSS_Signal_Hard_Output
PF6.PinAttribute=Appli
PF6.Signal=SPI5_NSS
PF7.GPIOParameters=GPIO_Label,PinAttribute
PF7.GPIO_Label=UART_TX/DOUT1
PF7.Mode=Asynchronous
PF7.PinAttribute=Appli
PF7.Signal=UART7_TX
PF9.GPIOParameters=PinAttribute
PF9.Mode=RGB888
PF9.PinAttribute=Appli
PF9.Signal=LTDC_R0
PG0.GPIOParameters=PinAttribute
PG0.Mode=RGB888
PG0.PinAttribute=Appli
PG0.Signal=LTDC_R7
PG1.GPIOParameters=PinAttribute
PG1.Mode=RGB888
PG1.PinAttribute=Appli
PG1.Signal=LTDC_R6
PG11.GPIOParameters=PinAttribute
PG11.Mode=RMII

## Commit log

2025-11-02 BOM update
2025-11-03 CEC and HPD signals fixed
2025-11-03 PCB layout improvement
2025-11-03 BOM update, PCB layout improvements, NetTie positions fixed
2025-11-11 Removed all blind/burned vias
2025-11-23 DIN3 pin assigned
2025-11-24 ETH clk fixed, digital I/O naming updated
2025-11-28 RTC input added
2025-12-22 #1, #2, #3
2026-01-17 Eth PHY straps updated
2026-01-17 POS files update
2026-01-17 Schematics update
